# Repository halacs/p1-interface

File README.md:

You can find my blog post [here](https://www.halacs.hu/electric-meter-reading).

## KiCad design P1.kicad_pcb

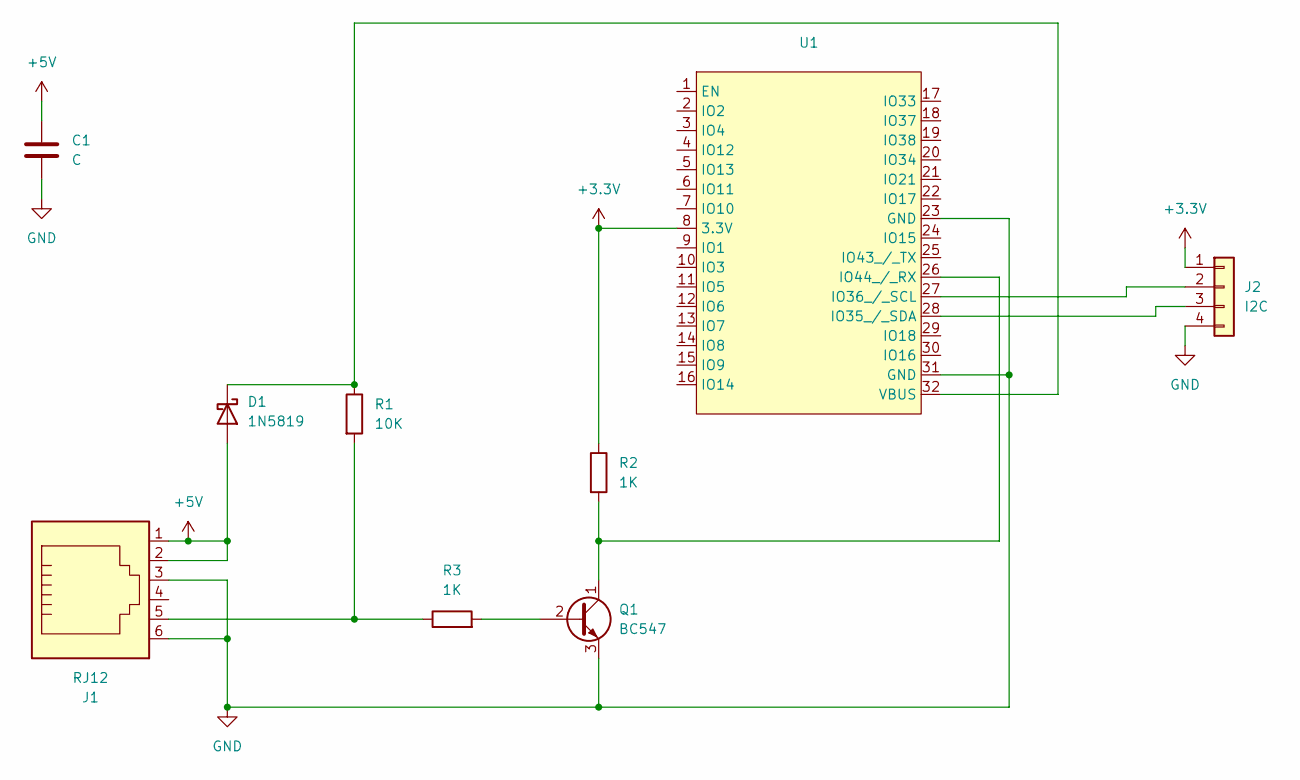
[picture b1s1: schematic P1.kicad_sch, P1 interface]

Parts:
C1: C; CP_Radial_Tantal_D10.5mm_P2.50mm
D1: 1N5819; D_DO-41_SOD81_P10.16mm_Horizontal
J1: RJ12; RJ25_Wayconn_MJEA-660X1_Horizontal
J2: I2C; PinHeader_1x04_P2.54mm_Vertical
Q1: BC547; TO-92_Inline
R1: 10K; R_Axial_DIN0411_L9.9mm_D3.6mm_P12.70mm_Horizontal
R2, R3: 1K; R_Axial_DIN0411_L9.9mm_D3.6mm_P12.70mm_Horizontal
U1: wemos s3 mini

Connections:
+3.3V: J2.1, R2.1, U1.8 (3.3V)
+5V: C1.1, D1.2 (A), J1.1, J1.2
GND: C1.2, J1.3, J1.6, J2.4, Q1.3 (E), U1.23 (GND), U1.31 (GND)
unnamed: D1.1 (K), R1.1, U1.32 (VBUS)
unnamed: J1.5, R1.2, R3.1
unnamed: J2.2, U1.27 (IO36_/_SCL)
unnamed: J2.3, U1.28 (IO35_/_SDA)
unnamed: Q1.2 (B), R3.2
unnamed: Q1.1 (C), R2.2, U1.26 (IO44_/_RX)

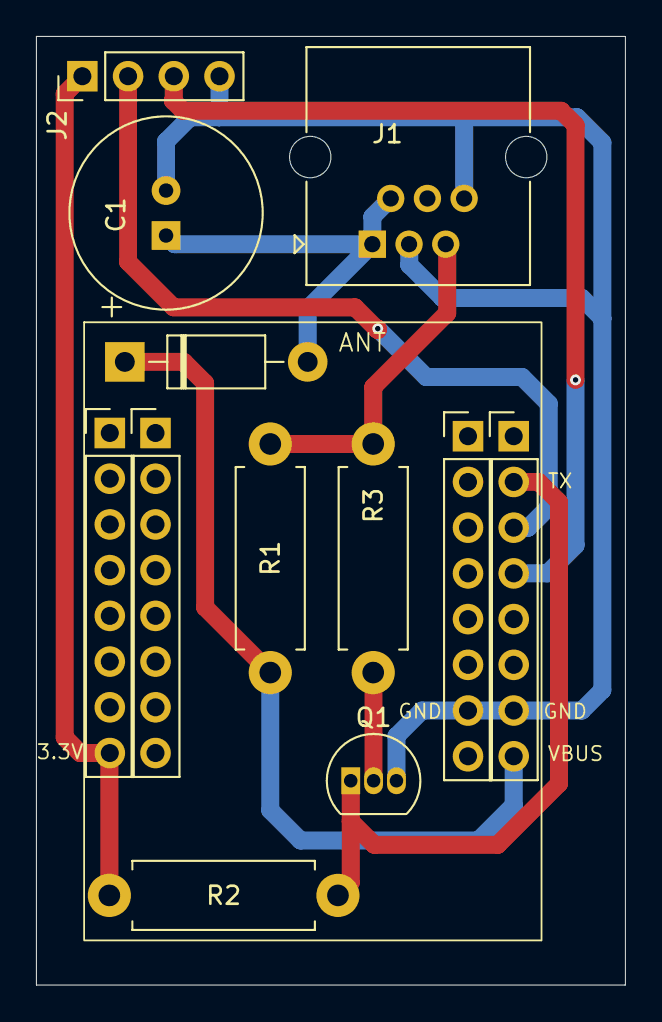
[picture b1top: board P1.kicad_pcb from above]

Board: 2 copper layers, 32.7 x 52.7 mm, 9 parts (0 on the bottom side), 9 nets.

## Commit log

2024-04-02 v1.0
